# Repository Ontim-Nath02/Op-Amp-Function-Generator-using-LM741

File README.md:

# A simple analog waveform generator designed using LM741 operational amplifiers.
This project was initially developed in Proteus Professional as part of an academic project.
Later, the same project was completely recreated in KiCad-9 as a personal learning project to practice:
1. schematic design,
2. PCB layout,
3. component placement,
4. and manual routing.
Both versions include the complete circuit design and PCB implementation.

# Project Overview

The circuit is an op-amp based waveform generator capable of producing square and triangle waveforms using oscillator and integrator stages.
This project helped in understanding:
1. Analog circuit design
2. Operational amplifier applications
3. RC timing circuits
4. PCB design workflow
5. Schematic capture and routing

# Development Workflow
# Academic — Proteus
1. Circuit design
2. Simulation and testing
3. Academic project implementation
# Learning — KiCad
1. Recreated the full schematic
2. Designed PCB layout
3. Manual routing and placement
4. PCB visualization and export

# Components Used
1. Op-Amps ---> LM741
2. Resistors	---> 1kΩ, 2.7kΩ, 10kΩ
3. Potentiometers	---> 10kΩ, 100kΩ
4. Capacitors	---> 22nF

# Proteus Schematic View

# KiCAD Schematic View 

# KiCAD PCB Editor View

# KiCAD 3D Front View

# KiCAD 3D Back View

# Applications
1. Electronics laboratory projects
2. Analog waveform generation
3. PCB design practice
4. Real and Educational op-amp experiments

# Created by 
Ontim Nath

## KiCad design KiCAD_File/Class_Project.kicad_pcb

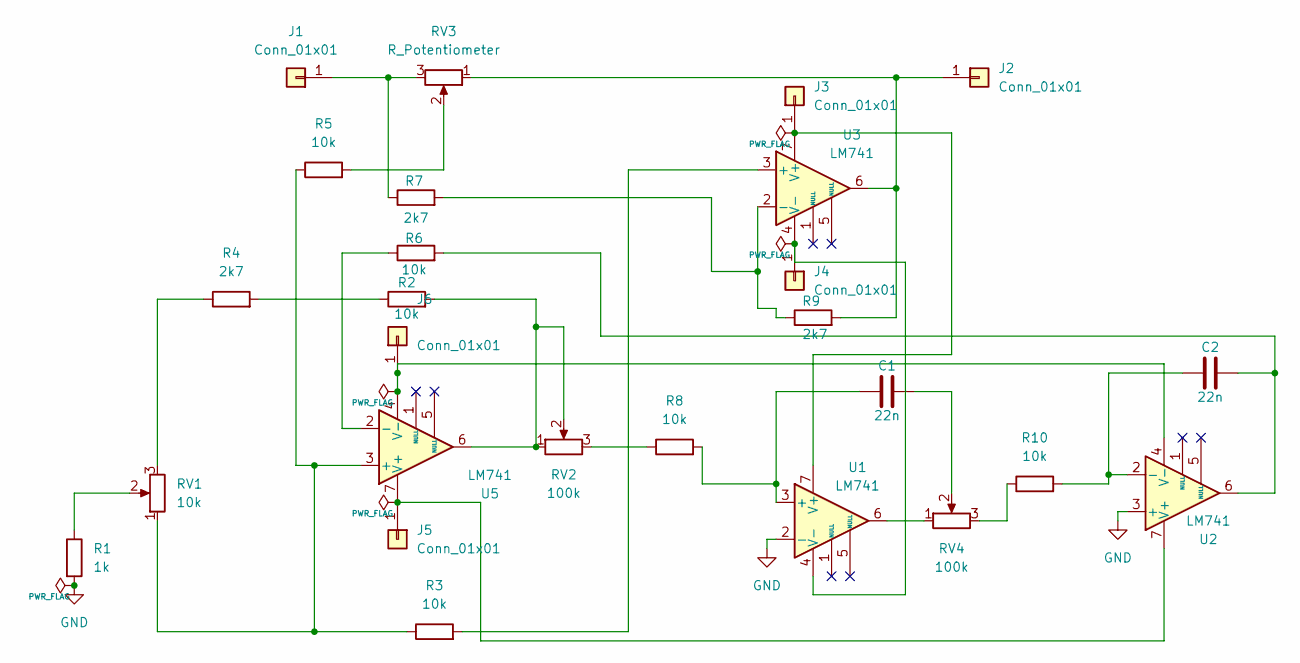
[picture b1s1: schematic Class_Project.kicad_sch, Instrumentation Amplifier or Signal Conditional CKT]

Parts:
C1, C2: 22n; C_Disc_D3.0mm_W1.6mm_P2.50mm
J1, J2, J3, J4, J5, J6: Conn_01x01; PinSocket_1x01_P2.54mm_Vertical
R1: 1k; R_Axial_DIN0204_L3.6mm_D1.6mm_P5.08mm_Horizontal
R2, R3, R5, R6, R8, R10: 10k; R_Axial_DIN0204_L3.6mm_D1.6mm_P5.08mm_Horizontal
R4, R7, R9: 2k7; R_Axial_DIN0204_L3.6mm_D1.6mm_P5.08mm_Horizontal
RV1: 10k; Potentiometer_ACP_CA6-H2,5_Horizontal
RV2, RV4: 100k; Potentiometer_ACP_CA6-H2,5_Horizontal
RV3: R_Potentiometer; Potentiometer_ACP_CA6-H2,5_Horizontal
U1, U2, U3, U5: LM741; DIP-8_W7.62mm

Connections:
GND: R1.2, U1.2 (-), U2.3 (+)
unnamed: C1.2, RV4.2
unnamed: C2.2, R6.2, U2.6
unnamed: J1.1, R7.1, RV3.3
unnamed: J2.1, R9.2, RV3.1, U3.6
unnamed: J3.1, U1.7 (V+), U3.7 (V+)
unnamed: J4.1, U1.4 (V-), U3.4 (V-)
unnamed: J5.1, U2.7 (V+), U5.7 (V+)
unnamed: J6.1, U2.4 (V-), U5.4 (V-)
unnamed: R1.1, RV1.2
unnamed: R2.1, R4.2
unnamed: R2.2, RV2.1, RV2.2, U5.6
unnamed: R4.1, RV1.3
unnamed: R5.2, RV3.2
unnamed: R8.1, RV2.3
unnamed: R10.1, RV4.3
unnamed: RV4.1, U1.6
unnamed: C1.1, R8.2, U1.3 (+)
unnamed: C2.1, R10.2, U2.2 (-)
unnamed: R3.2, U3.3 (+)
unnamed: R7.2, R9.1, U3.2 (-)
unnamed: R3.1, R5.1, RV1.1, U5.3 (+)
unnamed: R6.1, U5.2 (-)

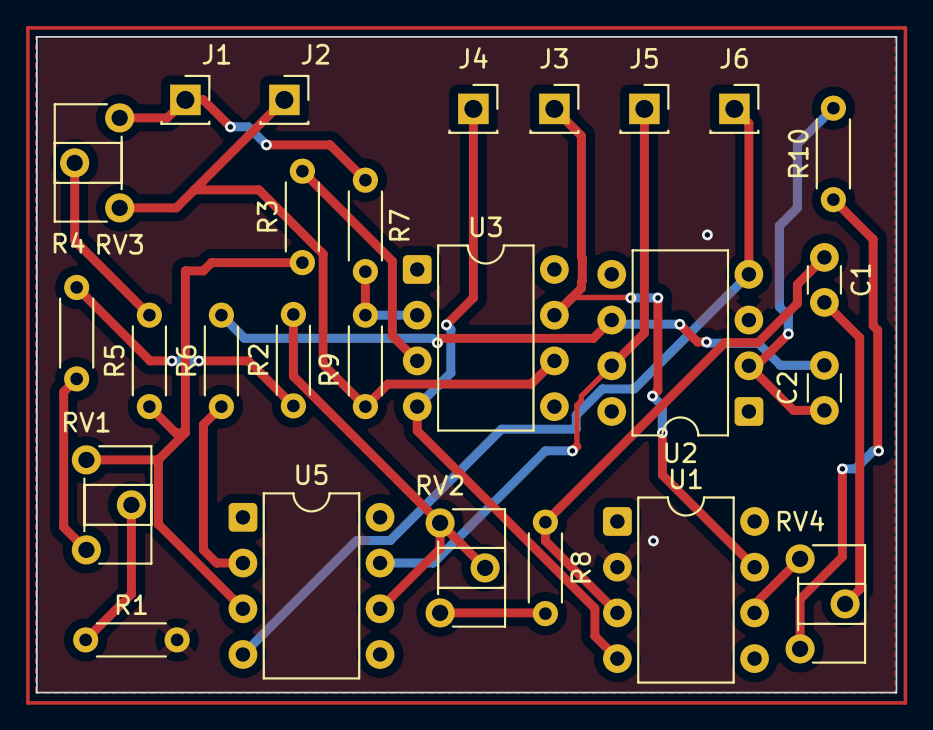
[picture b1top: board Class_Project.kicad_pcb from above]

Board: 2 copper layers, 47.8 x 36.4 mm, 26 parts (0 on the bottom side), 23 nets.
